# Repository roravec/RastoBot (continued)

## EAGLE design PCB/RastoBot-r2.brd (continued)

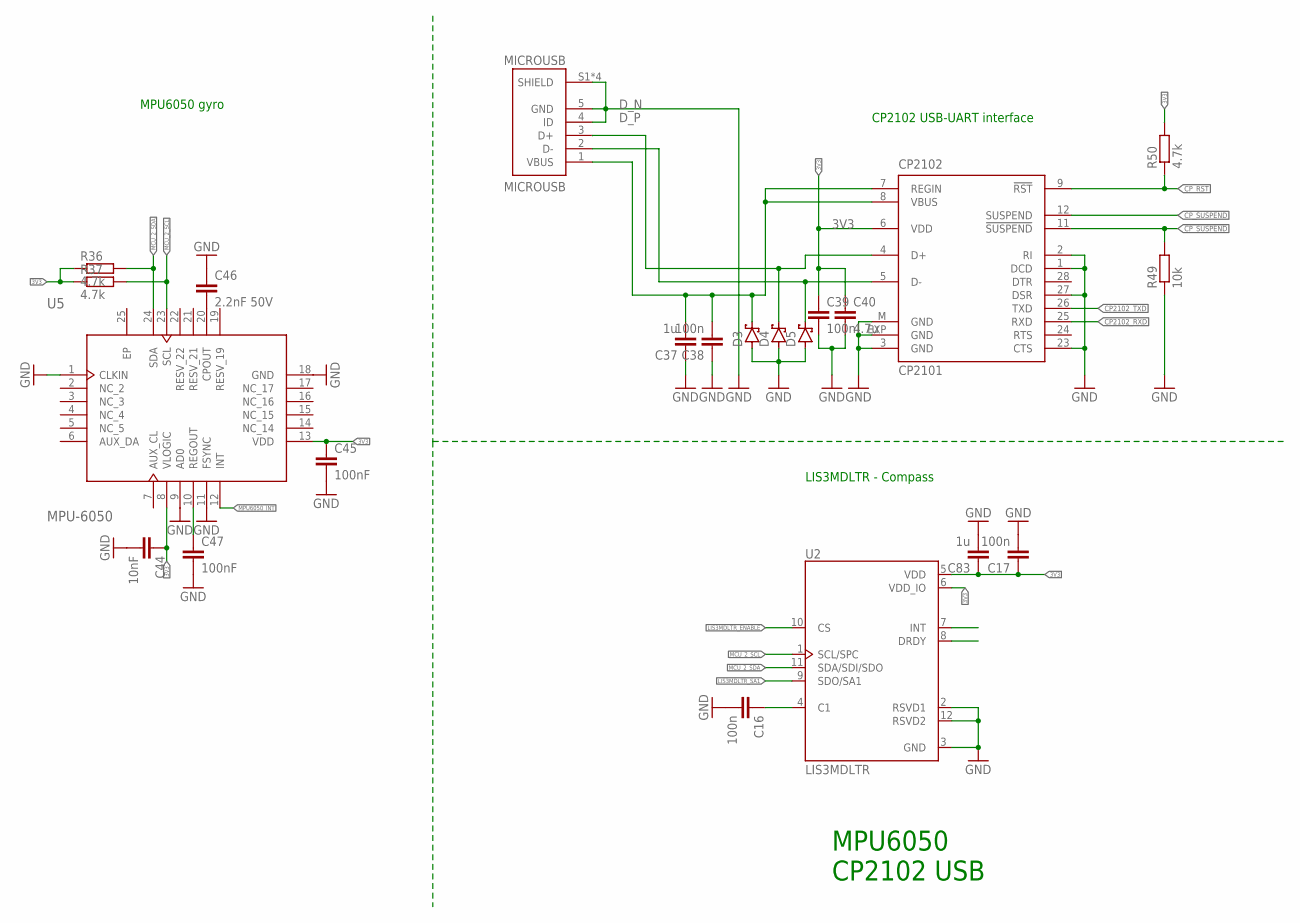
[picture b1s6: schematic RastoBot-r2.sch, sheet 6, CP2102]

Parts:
C16, C17, C38, C39: 100n; C0603
C37, C83: 1u; C0603
C40: 4.7u; C0603
C44: 10nF; C0603
C45, C47: 100nF; C0603
C46: 2.2nF 50V; C0603
CP2102: CP2101; MLP28
D3, D4, D5: BAT60J; SOD323_ST
MICROUSB: MICROUSB; MOLEX_47642-0001
R36, R37, R50: 4.7k; R0603
R49: 10k; R0603
U2: LIS3MDLTR; XDCR_LIS3MDLTR
U5: MPU-6050; 24-VFQFN

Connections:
3V3: C17.1, C39.1, C40.1, C44.1, C45.1, C83.1, CP2102.6 (VDD), R36.1, R37.1, R50.2, U2.5 (VDD), U2.6 (VDD_IO), U5.8 (VLOGIC), U5.13 (VDD); also elsewhere on the board
!CP_SUSPEND: CP2102.11 (!SUSPEND), R49.2
CP2102_RXD: CP2102.25 (RXD); also elsewhere on the board
CP2102_TXD: CP2102.26 (TXD); also elsewhere on the board
CP_RST: CP2102.9 (!RST), R50.1
CP_SUSPEND: CP2102.12 (SUSPEND)
D_N: CP2102.5 (D-), D5.C, MICROUSB.2 (D-)
D_P: CP2102.4 (D+), D4.C, MICROUSB.3 (D+)
EP: U5.25 (EP)
GND: C16.2, C17.2, C37.1, C38.1, C39.2, C40.2, C44.2, C45.2, C46.1, C47.2, C83.2, CP2102.1 (DCD), CP2102.2 (RI), CP2102.3 (GND), CP2102.23 (CTS), CP2102.27 (DSR), CP2102.EXP (GND), CP2102.M (GND), D3.A, D4.A, D5.A, MICROUSB.4 (ID), MICROUSB.5 (GND), MICROUSB.S1 (SHIELD), MICROUSB.S2 (SHIELD), MICROUSB.S3 (SHIELD), MICROUSB.S4 (SHIELD), R49.1, U2.2 (RSVD1), U2.3 (GND), U2.12 (RSVD2), U5.1 (CLKIN), U5.9 (AD0), U5.11 (FSYNC), U5.18 (GND); also elsewhere on the board
LIS3MDLTR_ENABLE: U2.10 (CS)
LIS3MDLTR_SA1: U2.9 (SDO/SA1)
MCU_2_SCL: R37.2, U2.1 (SCL/SPC), U5.23 (SCL); also elsewhere on the board
MCU_2_SDA: R36.2, U2.11 (SDA/SDI/SDO), U5.24 (SDA); also elsewhere on the board
MPU6050_INT: U5.12 (INT)
unnamed: C37.2, C38.2, CP2102.7 (REGIN), CP2102.8 (VBUS), D3.C, MICROUSB.1 (VBUS)
unnamed: C46.2, U5.20 (CPOUT)
unnamed: C47.1, U5.10 (REGOUT)
unnamed: C16.1, U2.4 (C1)

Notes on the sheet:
MPU6050 CP2102 USB
MPU6050 gyro
CP2102 USB-UART interface
LIS3MDLTR - Compass

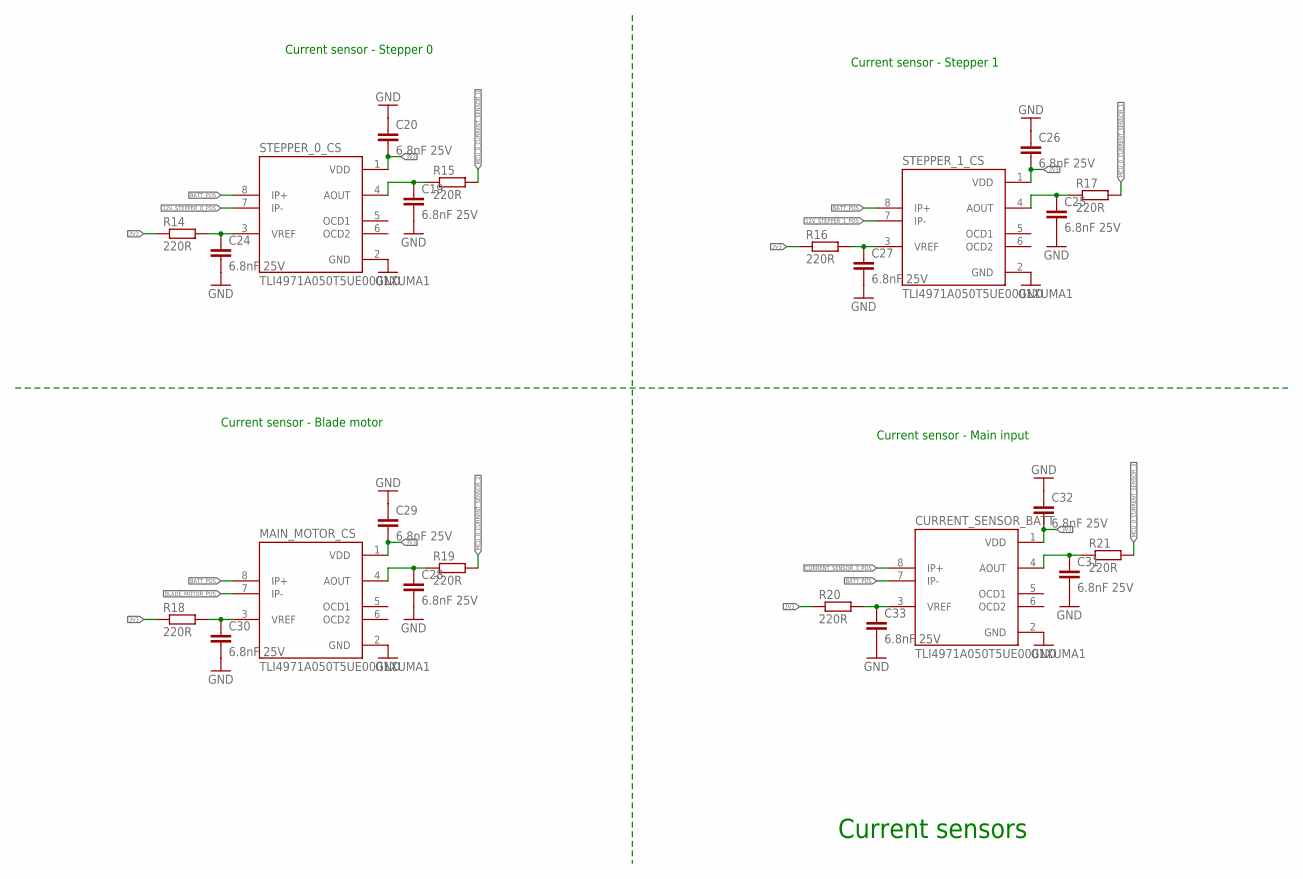
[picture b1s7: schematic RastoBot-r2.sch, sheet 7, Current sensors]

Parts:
C19, C20, C24, C25, C26, C27, C28, C29, C30, C31, C32, C33: 6.8nF 25V; C0603
CURRENT_SENSOR_BATT: TLI4971A050T5UE0001XUMA1; IC_TLI4971A050T5UE0001XUMA1
MAIN_MOTOR_CS: TLI4971A050T5UE0001XUMA1; IC_TLI4971A050T5UE0001XUMA1
R14, R15, R16, R17, R18, R19, R20, R21: 220R; R0805
STEPPER_0_CS, STEPPER_1_CS: TLI4971A050T5UE0001XUMA1; IC_TLI4971A050T5UE0001XUMA1

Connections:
3V3: C20.2, C26.2, C29.2, C32.2, CURRENT_SENSOR_BATT.1 (VDD), MAIN_MOTOR_CS.1 (VDD), R14.1, R16.1, R18.1, R20.1, STEPPER_0_CS.1 (VDD), STEPPER_1_CS.1 (VDD); also elsewhere on the board
12V_STEPPER_0_POS: STEPPER_0_CS.7 (IP-); also elsewhere on the board
12V_STEPPER_1_POS: STEPPER_1_CS.7 (IP-); also elsewhere on the board
BATT_POS: CURRENT_SENSOR_BATT.7 (IP-), MAIN_MOTOR_CS.8 (IP+), STEPPER_0_CS.8 (IP+), STEPPER_1_CS.8 (IP+); also elsewhere on the board
BLADE_MOTOR_POS: MAIN_MOTOR_CS.7 (IP-); also elsewhere on the board
CURRENT_SENSOR_3_POS: CURRENT_SENSOR_BATT.8 (IP+); also elsewhere on the board
GND: C19.2, C20.1, C24.2, C25.2, C26.1, C27.2, C28.2, C29.1, C30.2, C31.2, C32.1, C33.2, CURRENT_SENSOR_BATT.2 (GND), MAIN_MOTOR_CS.2 (GND), STEPPER_0_CS.2 (GND), STEPPER_1_CS.2 (GND); also elsewhere on the board
MCU_0_CURRENT_SENSOR_0: R15.2; also elsewhere on the board
MCU_0_CURRENT_SENSOR_1: R17.2; also elsewhere on the board
MCU_0_CURRENT_SENSOR_2: R19.2; also elsewhere on the board
MCU_0_CURRENT_SENSOR_3: R21.2; also elsewhere on the board
unnamed: C19.1, R15.1, STEPPER_0_CS.4 (AOUT)
unnamed: C27.1, R16.2, STEPPER_1_CS.3 (VREF)
unnamed: C25.1, R17.1, STEPPER_1_CS.4 (AOUT)
unnamed: C24.1, R14.2, STEPPER_0_CS.3 (VREF)
unnamed: C30.1, MAIN_MOTOR_CS.3 (VREF), R18.2
unnamed: C28.1, MAIN_MOTOR_CS.4 (AOUT), R19.1
unnamed: C33.1, CURRENT_SENSOR_BATT.3 (VREF), R20.2
unnamed: C31.1, CURRENT_SENSOR_BATT.4 (AOUT), R21.1

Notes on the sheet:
Current sensors
Current sensor - Stepper 0
Current sensor - Stepper 1
Current sensor - Blade motor
Current sensor - Main input

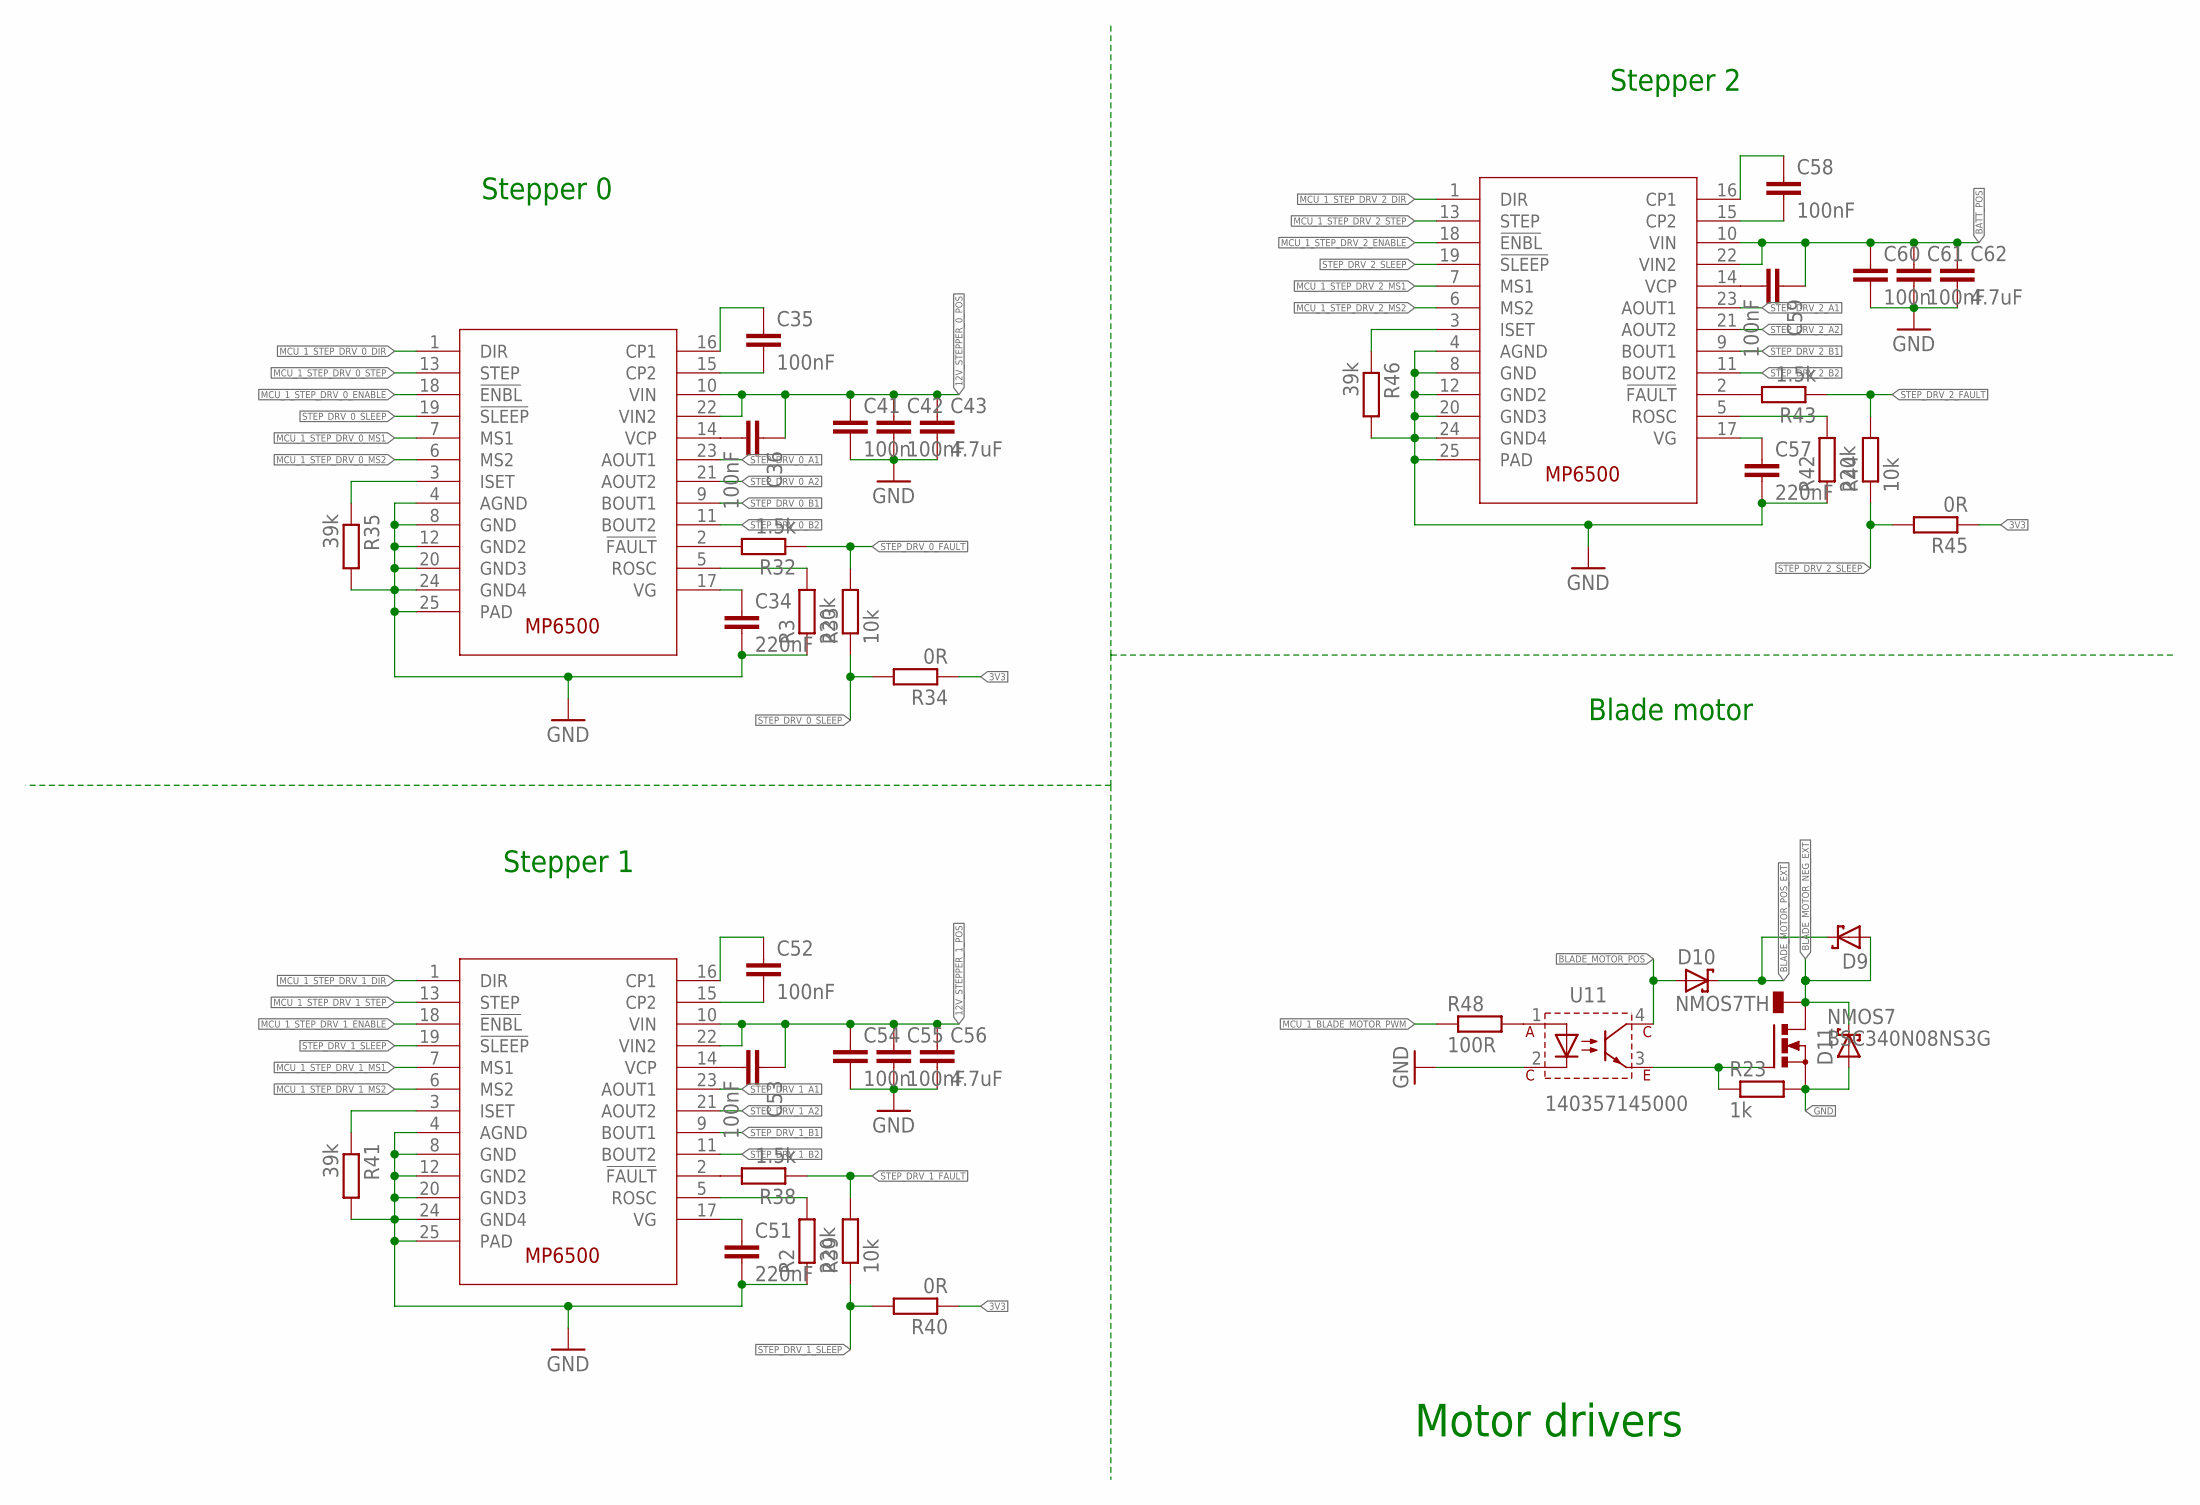
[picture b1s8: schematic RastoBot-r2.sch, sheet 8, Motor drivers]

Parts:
C34, C51, C57: 220nF; C0603
C35, C36, C42, C52, C53, C55, C58, C59, C61: 100nF; C0603
C41, C54, C60: 100n; C0603
C43, C56, C62: 4.7uF; C0603
D9, D10, D11: SCHOTTKY-DIODEAG; AG
NMOS7: BSC340N08NS3G; PG-TDSON-8
R2, R3, R42: 220k; R0603
R23: 1k; R0805
R32, R38, R43: 1.5k; R0603
R33, R39, R44: 10k; R0603
R34, R40, R45: 0R; R0603
R35, R41, R46: 39k; R0603
R48: 100R; R0805
SD1, SD2, SD3: MP6500; QFN65P500X500X100-25N
U11: 140357145000; WL-OCPT_SOP4

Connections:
3V3: R34.1, R40.1, R45.1; also elsewhere on the board
12V_STEPPER_0_POS: C36.1, C41.1, C42.1, C43.1, SD1.10 (VIN), SD1.22 (VIN2); also elsewhere on the board
12V_STEPPER_1_POS: C53.1, C54.1, C55.1, C56.1, SD2.10 (VIN), SD2.22 (VIN2); also elsewhere on the board
BATT_POS: C59.1, C60.1, C61.1, C62.1, SD3.10 (VIN), SD3.22 (VIN2); also elsewhere on the board
BLADE_MOTOR_NEG_EXT: D9.A, D11.C, NMOS7.5 (D), NMOS7.6 (D), NMOS7.7 (D), NMOS7.8 (D), NMOS7.TH; also elsewhere on the board
BLADE_MOTOR_POS: D10.A, U11.4; also elsewhere on the board
BLADE_MOTOR_POS_EXT: D9.C, D10.C; also elsewhere on the board
GND: C34.2, C41.2, C42.2, C43.2, C51.2, C54.2, C55.2, C56.2, C57.2, C60.2, C61.2, C62.2, D11.A, NMOS7.1 (S), NMOS7.2 (S), NMOS7.3 (S), R2.1, R3.1, R23.2, R35.2, R41.2, R42.1, R46.2, SD1.4 (AGND), SD1.8 (GND), SD1.12 (GND2), SD1.20 (GND3), SD1.24 (GND4), SD1.25 (PAD), SD2.4 (AGND), SD2.8 (GND), SD2.12 (GND2), SD2.20 (GND3), SD2.24 (GND4), SD2.25 (PAD), SD3.4 (AGND), SD3.8 (GND), SD3.12 (GND2), SD3.20 (GND3), SD3.24 (GND4), SD3.25 (PAD), U11.2; also elsewhere on the board
MCU_1_BLADE_MOTOR_PWM: R48.1; also elsewhere on the board
MCU_1_STEP_DRV_0_DIR: SD1.1 (DIR); also elsewhere on the board
MCU_1_STEP_DRV_0_ENABLE: SD1.18 (!ENBL); also elsewhere on the board
MCU_1_STEP_DRV_0_MS1: SD1.7 (MS1); also elsewhere on the board
MCU_1_STEP_DRV_0_MS2: SD1.6 (MS2); also elsewhere on the board
MCU_1_STEP_DRV_0_STEP: SD1.13 (STEP); also elsewhere on the board
MCU_1_STEP_DRV_1_DIR: SD2.1 (DIR); also elsewhere on the board
MCU_1_STEP_DRV_1_ENABLE: SD2.18 (!ENBL); also elsewhere on the board
MCU_1_STEP_DRV_1_MS1: SD2.7 (MS1); also elsewhere on the board
MCU_1_STEP_DRV_1_MS2: SD2.6 (MS2); also elsewhere on the board
MCU_1_STEP_DRV_1_STEP: SD2.13 (STEP); also elsewhere on the board
MCU_1_STEP_DRV_2_DIR: SD3.1 (DIR); also elsewhere on the board
MCU_1_STEP_DRV_2_ENABLE: SD3.18 (!ENBL); also elsewhere on the board
MCU_1_STEP_DRV_2_MS1: SD3.7 (MS1); also elsewhere on the board
MCU_1_STEP_DRV_2_MS2: SD3.6 (MS2); also elsewhere on the board
MCU_1_STEP_DRV_2_STEP: SD3.13 (STEP); also elsewhere on the board
unnamed: C34.1, SD1.17 (VG)
unnamed: R3.2, SD1.5 (ROSC)
unnamed: R48.2, U11.1
unnamed: NMOS7.4 (G), R23.1, U11.3
unnamed: C35.2, SD1.15 (CP2)
unnamed: C35.1, SD1.16 (CP1)
unnamed: R32.2, SD1.2 (!FAULT)
unnamed: C36.2, SD1.14 (VCP)
unnamed: C51.1, SD2.17 (VG)
unnamed: R35.1, SD1.3 (ISET)
unnamed: R2.2, SD2.5 (ROSC)
unnamed: C52.2, SD2.15 (CP2)
unnamed: C52.1, SD2.16 (CP1)
unnamed: C53.2, SD2.14 (VCP)
unnamed: R41.1, SD2.3 (ISET)
unnamed: R38.2, SD2.2 (!FAULT)
unnamed: C57.1, SD3.17 (VG)
unnamed: R42.2, SD3.5 (ROSC)
unnamed: C58.2, SD3.15 (CP2)
unnamed: C58.1, SD3.16 (CP1)
unnamed: C59.2, SD3.14 (VCP)
unnamed: R46.1, SD3.3 (ISET)
unnamed: R43.2, SD3.2 (!FAULT)
STEP_DRV_0_A1: SD1.23 (AOUT1); also elsewhere on the board
STEP_DRV_0_A2: SD1.21 (AOUT2); also elsewhere on the board
STEP_DRV_0_B1: SD1.9 (BOUT1); also elsewhere on the board
STEP_DRV_0_B2: SD1.11 (BOUT2); also elsewhere on the board
STEP_DRV_0_FAULT: R32.1, R33.2
STEP_DRV_0_SLEEP: R33.1, R34.2, SD1.19 (!SLEEP)
STEP_DRV_1_A1: SD2.23 (AOUT1); also elsewhere on the board
STEP_DRV_1_A2: SD2.21 (AOUT2); also elsewhere on the board
STEP_DRV_1_B1: SD2.9 (BOUT1); also elsewhere on the board
STEP_DRV_1_B2: SD2.11 (BOUT2); also elsewhere on the board
STEP_DRV_1_FAULT: R38.1, R39.2
STEP_DRV_1_SLEEP: R39.1, R40.2, SD2.19 (!SLEEP)
STEP_DRV_2_A1: SD3.23 (AOUT1); also elsewhere on the board
STEP_DRV_2_A2: SD3.21 (AOUT2); also elsewhere on the board
STEP_DRV_2_B1: SD3.9 (BOUT1); also elsewhere on the board
STEP_DRV_2_B2: SD3.11 (BOUT2); also elsewhere on the board
STEP_DRV_2_FAULT: R43.1, R44.2
STEP_DRV_2_SLEEP: R44.1, R45.2, SD3.19 (!SLEEP)

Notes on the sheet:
Stepper 0
Stepper 1
Stepper 2
Blade motor
Motor drivers

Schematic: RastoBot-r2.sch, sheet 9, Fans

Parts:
EM_LIGHT: EMERGENCY LIGHT; 1X02
FAN_0: FAN_0; 1X02
FAN_1: FAN_1; 1X02
FAN_2: FAN_2; 1X02
FAN_3: FAN_3; 1X02
NMOS2, NMOS3, NMOS4, NMOS5, NMOS6: BSC340N08NS3G; PG-TDSON-8
R22, R51, R52, R53, R119: 200R; R0805
R63, R65, R67, R68, R76: 1k; R0805
U4, U6, U7, U8, U12: 140357145000; WL-OCPT_SOP4

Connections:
BATT_POS: EM_LIGHT.1, FAN_0.1, FAN_1.1, FAN_2.1, FAN_3.1, U4.4, U6.4, U7.4, U8.4, U12.4; also elsewhere on the board
GND: NMOS2.1 (S), NMOS2.2 (S), NMOS2.3 (S), NMOS3.1 (S), NMOS3.2 (S), NMOS3.3 (S), NMOS4.1 (S), NMOS4.2 (S), NMOS4.3 (S), NMOS5.1 (S), NMOS5.2 (S), NMOS5.3 (S), NMOS6.1 (S), NMOS6.2 (S), NMOS6.3 (S), R63.2, R65.2, R67.2, R68.2, R76.2, U4.2, U6.2, U7.2, U8.2, U12.2; also elsewhere on the board
MCU_0_EMERGENCY_LIGHT: R119.1; also elsewhere on the board
MCU_0_FAN_0: R22.1; also elsewhere on the board
MCU_0_FAN_1: R51.1; also elsewhere on the board
MCU_0_FAN_2: R53.1; also elsewhere on the board
MCU_0_FAN_3: R52.1; also elsewhere on the board
unnamed: NMOS6.4 (G), R68.1, U12.3
unnamed: EM_LIGHT.2, NMOS6.5 (D), NMOS6.6 (D), NMOS6.7 (D), NMOS6.8 (D), NMOS6.TH
unnamed: R119.2, U12.1
unnamed: R22.2, U4.1
unnamed: FAN_0.2, NMOS2.5 (D), NMOS2.6 (D), NMOS2.7 (D), NMOS2.8 (D), NMOS2.TH
unnamed: R51.2, U6.1
unnamed: R52.2, U8.1
unnamed: NMOS2.4 (G), R76.1, U4.3
unnamed: NMOS3.4 (G), R63.1, U6.3
unnamed: FAN_1.2, NMOS3.5 (D), NMOS3.6 (D), NMOS3.7 (D), NMOS3.8 (D), NMOS3.TH
unnamed: R53.2, U7.1
unnamed: NMOS4.4 (G), R65.1, U7.3
unnamed: FAN_2.2, NMOS4.5 (D), NMOS4.6 (D), NMOS4.7 (D), NMOS4.8 (D), NMOS4.TH
unnamed: NMOS5.4 (G), R67.1, U8.3
unnamed: FAN_3.2, NMOS5.5 (D), NMOS5.6 (D), NMOS5.7 (D), NMOS5.8 (D), NMOS5.TH

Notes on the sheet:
Fan_0
Fan_1
Fan_2
Fan_3
Fan drivers Emergency light switch
Emergency light

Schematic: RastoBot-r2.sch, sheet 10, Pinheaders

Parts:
C63, C64, C65, C66: 1u; C0603
D2: 3V3; SOD80C
GPS: GPS MODULE; 1X05
LIDAR: LIDAR; 1X08
LIGHT_SENSOR: PHOTORESISTOR LDR5549; 1X02
LIMIT_SWITCH_DOWN: LIMIT_SWITCH_BOTTOM_MAGNETIC; 1X03
LIMIT_SWITCH_UP: LIMIT_SWITCH_UPPER_MAGNETIC; 1X03
MAIN_MOTOR: MAIN MOTOR; 1X04
MCU_2_I2C_EXTENDER: MCU_2_I2C_EXTENDER; 1X04
NAVIGATION_UART: TELEMETRY_UART; 1X02
NMOS1: BSC340N08NS3G; PG-TDSON-8
PERIMETER_WIRE: PER.WIRE SENSE; 1X04
R4, R54: 1k; R0805
R55, R64: 500k; R0805
R57, R66: 10R; R0805
R62: 200R; R0805
R69, R71, R72: 5k; R0805
R70: 5k; R0603
R107, R108, R109, R110: 10k; R0805
RAIN_SENSOR: RAIN SENSOR; 1X02
STEPPER_0: STEPPER_0; 1X04
STEPPER_1: STEPPER_1; 1X04
STEPPER_2: STEPPER_2; 1X04
TEMP_SENSOR_0: TEMP SENSOR 0; 1X03
TEMP_SENSOR_1: TEMP SENSOR 1; 1X03
TEMP_SENSOR_2: TEMP SENSOR 2; 1X03
TEMP_SENSOR_3: TEMP SENSOR 3; 1X03
U10: 140357145000; WL-OCPT_SOP4
UNLIMITED_POWER: V_OUTPUT; 1X05

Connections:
3V3: C63.2, C64.2, C65.2, C66.2, GPS.1, LIMIT_SWITCH_DOWN.1, LIMIT_SWITCH_UP.1, MCU_2_I2C_EXTENDER.3, R55.1, R64.1, R69.2, R70.2, R71.2, R72.2, TEMP_SENSOR_0.1, TEMP_SENSOR_1.1, TEMP_SENSOR_2.1, TEMP_SENSOR_3.1, UNLIMITED_POWER.1; also elsewhere on the board
5V: LIDAR.2, PERIMETER_WIRE.1, U10.4, UNLIMITED_POWER.2; also elsewhere on the board
BATT_POS: UNLIMITED_POWER.3; also elsewhere on the board
BLADE_MOTOR_NEG_EXT: MAIN_MOTOR.3, MAIN_MOTOR.4; also elsewhere on the board
BLADE_MOTOR_POS_EXT: MAIN_MOTOR.1, MAIN_MOTOR.2; also elsewhere on the board
GND: C63.1, C64.1, C65.1, C66.1, D2.A, GPS.2, LIDAR.1, LIGHT_SENSOR.2, LIMIT_SWITCH_DOWN.3, LIMIT_SWITCH_UP.3, MCU_2_I2C_EXTENDER.4, NMOS1.1 (S), NMOS1.2 (S), NMOS1.3 (S), PERIMETER_WIRE.3, PERIMETER_WIRE.4, R54.2, R109.1, R110.1, RAIN_SENSOR.2, TEMP_SENSOR_0.3, TEMP_SENSOR_1.3, TEMP_SENSOR_2.3, TEMP_SENSOR_3.3, U10.2, UNLIMITED_POWER.4, UNLIMITED_POWER.5; also elsewhere on the board
GPS_PPS: GPS.5
GPS_RXD: GPS.4; also elsewhere on the board
GPS_TXD: GPS.3; also elsewhere on the board
LIDAR_RX: LIDAR.4; also elsewhere on the board
LIDAR_TX: LIDAR.7; also elsewhere on the board
LIMIT_SWITCH_BOTTOM: R108.1; also elsewhere on the board
LIMIT_SWITCH_UPPER: R107.1; also elsewhere on the board
MCU_0_LIGHT_SENSOR: R66.1; also elsewhere on the board
MCU_0_RAIN_SENSOR: R57.1; also elsewhere on the board
MCU_0_TEMP_SENSOR_0: R69.1, TEMP_SENSOR_0.2; also elsewhere on the board
MCU_0_TEMP_SENSOR_1: R70.1, TEMP_SENSOR_1.2; also elsewhere on the board
MCU_0_TEMP_SENSOR_2: R71.1, TEMP_SENSOR_2.2; also elsewhere on the board
MCU_0_TEMP_SENSOR_3: R72.1, TEMP_SENSOR_3.2; also elsewhere on the board
MCU_2_LIDAR_ENABLE: R62.1; also elsewhere on the board
MCU_2_SCL: MCU_2_I2C_EXTENDER.2; also elsewhere on the board
MCU_2_SDA: MCU_2_I2C_EXTENDER.1; also elsewhere on the board
MCU_3_UART2_RX: NAVIGATION_UART.1; also elsewhere on the board
MCU_3_UART2_TX: NAVIGATION_UART.2; also elsewhere on the board
unnamed: PERIMETER_WIRE.2, R4.2
unnamed: LIDAR.5, NMOS1.5 (D), NMOS1.6 (D), NMOS1.7 (D), NMOS1.8 (D), NMOS1.TH
unnamed: LIGHT_SENSOR.1, R64.2, R66.2
unnamed: NMOS1.4 (G), R54.1, U10.3
unnamed: R55.2, R57.2, RAIN_SENSOR.1
unnamed: R62.2, U10.1
unnamed: LIMIT_SWITCH_DOWN.2, R108.2, R109.2
unnamed: LIMIT_SWITCH_UP.2, R107.2, R110.2
PERIMETER_WIRE_SENSE: D2.C, R4.1; also elsewhere on the board
STEP_DRV_0_A1: STEPPER_0.1; also elsewhere on the board
STEP_DRV_0_A2: STEPPER_0.2; also elsewhere on the board
STEP_DRV_0_B1: STEPPER_0.3; also elsewhere on the board
STEP_DRV_0_B2: STEPPER_0.4; also elsewhere on the board
STEP_DRV_1_A1: STEPPER_1.1; also elsewhere on the board
STEP_DRV_1_A2: STEPPER_1.2; also elsewhere on the board
STEP_DRV_1_B1: STEPPER_1.3; also elsewhere on the board
STEP_DRV_1_B2: STEPPER_1.4; also elsewhere on the board
STEP_DRV_2_A1: STEPPER_2.1; also elsewhere on the board
STEP_DRV_2_A2: STEPPER_2.2; also elsewhere on the board
STEP_DRV_2_B1: STEPPER_2.3; also elsewhere on the board
STEP_DRV_2_B2: STEPPER_2.4; also elsewhere on the board

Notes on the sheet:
GPS TXD to MCU RX!
Resistance is between 10M (dry) to less than 1M (fully wet)
Blade motor
Stepper_0
Stepper_1
Stepper_2
GPS
Rain sensor
Mechanical limit switches
Temperature sensor DHT11
Perimeter wire sense
Lidar
Magnetic limit switches
Pinheaders
Resistance is between 10M (dark) to less than 100k (daylight)
Light sensor
MCU_2_I2C Extender

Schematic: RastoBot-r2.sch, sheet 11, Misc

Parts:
BATT: TPB1,27; B1,27
BATT_POS: TPB1,27; B1,27
CP2102_RX, CP2102_TX: TPB1,27; B1,27
CS_BATT: TPB1,27; B1,27
CS_MAIN_MOT: TPB1,27; B1,27
CS_STEP0, CS_STEP1: TPB1,27; B1,27
GPS_RX: TPB1,27; B1,27
GPS_TX: TPB1,27; B1,27
H1, H2, H3, H4, H5, H6: MOUNT-PAD-ROUND3.0; 3,0-PAD
LIDAR_RX: TPB1,27; B1,27
LIDAR_TX: TPB1,27; B1,27
MCU0_RX, MCU0_TX, MCU1_RX, MCU1_TX, MCU3_RX, MCU3_SCL, MCU3_SDA, MCU3_TX: TPB1,27; B1,27
MPU6050_SCL, MPU6050_SDA: TPB1,27; B1,27
PERIM: TPB1,27; B1,27
TILT: TPB1,27; B1,27
TP2, TP3: TPB1,27; B1,27

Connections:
3V3: TP3.TP; also elsewhere on the board
5V: TP2.TP; also elsewhere on the board
BATT_DIRECT_POS_POLE: BATT.TP; also elsewhere on the board
BATT_POS: BATT_POS.TP; also elsewhere on the board
CP2102_RXD: CP2102_RX.TP; also elsewhere on the board
CP2102_TXD: CP2102_TX.TP; also elsewhere on the board
GPS_RXD: GPS_RX.TP; also elsewhere on the board
GPS_TXD: GPS_TX.TP; also elsewhere on the board
LIDAR_RX: LIDAR_RX.TP; also elsewhere on the board
LIDAR_TX: LIDAR_TX.TP; also elsewhere on the board
MCU_0_CURRENT_SENSOR_0: CS_STEP0.TP; also elsewhere on the board
MCU_0_CURRENT_SENSOR_1: CS_STEP1.TP; also elsewhere on the board
MCU_0_CURRENT_SENSOR_2: CS_MAIN_MOT.TP; also elsewhere on the board
MCU_0_CURRENT_SENSOR_3: CS_BATT.TP; also elsewhere on the board
MCU_0_TILT_SENSOR: TILT.TP; also elsewhere on the board
MCU_0_UART_RX: MCU0_RX.TP; also elsewhere on the board
MCU_0_UART_TX: MCU0_TX.TP; also elsewhere on the board
MCU_1_UART1_RX: MCU1_RX.TP; also elsewhere on the board
MCU_1_UART1_TX: MCU1_TX.TP; also elsewhere on the board
MCU_2_SCL: MPU6050_SCL.TP; also elsewhere on the board
MCU_2_SDA: MPU6050_SDA.TP; also elsewhere on the board
MCU_3_I2C_SCL: MCU3_SCL.TP; also elsewhere on the board
MCU_3_I2C_SDA: MCU3_SDA.TP; also elsewhere on the board
MCU_3_UART1_RX: MCU3_RX.TP; also elsewhere on the board
MCU_3_UART1_TX: MCU3_TX.TP; also elsewhere on the board
PERIMETER_WIRE_SENSE: PERIM.TP; also elsewhere on the board

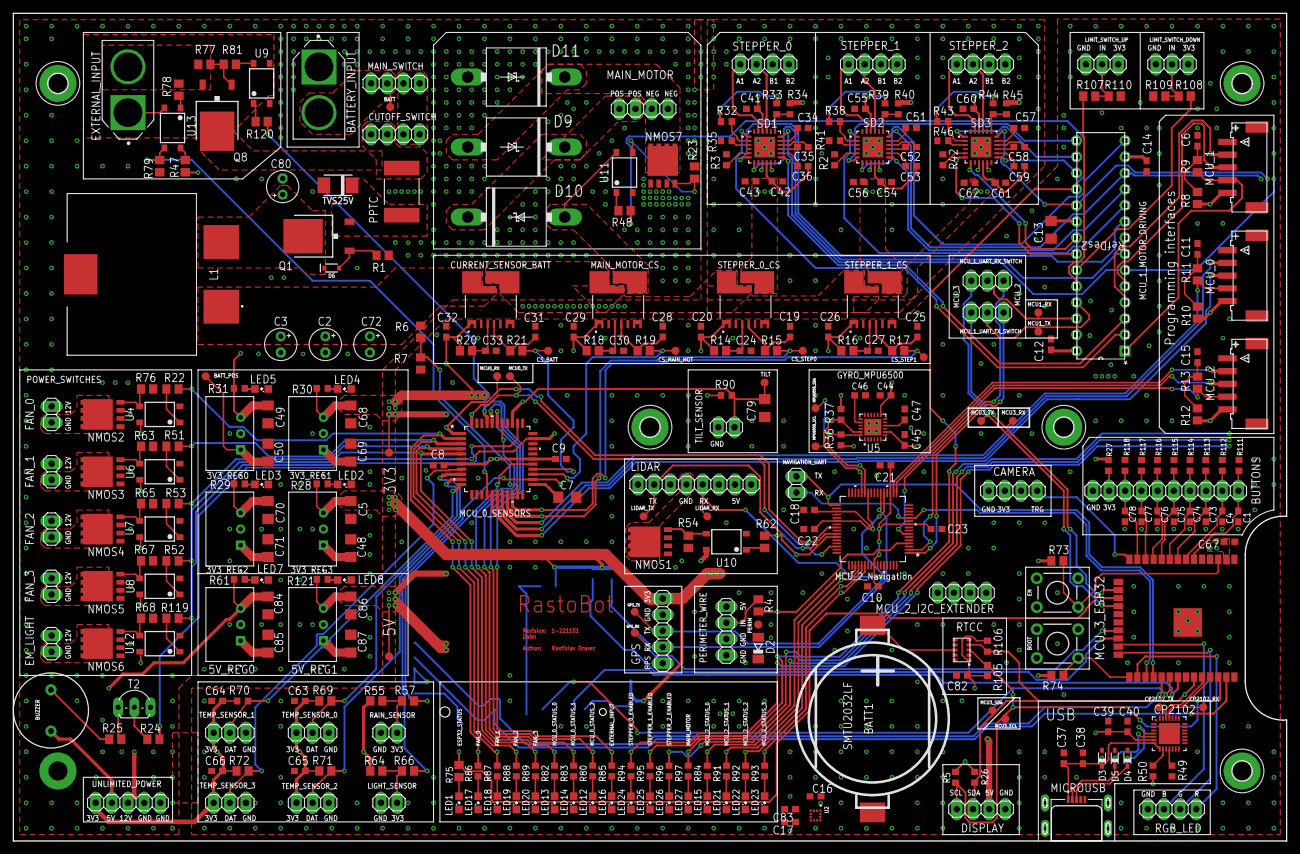
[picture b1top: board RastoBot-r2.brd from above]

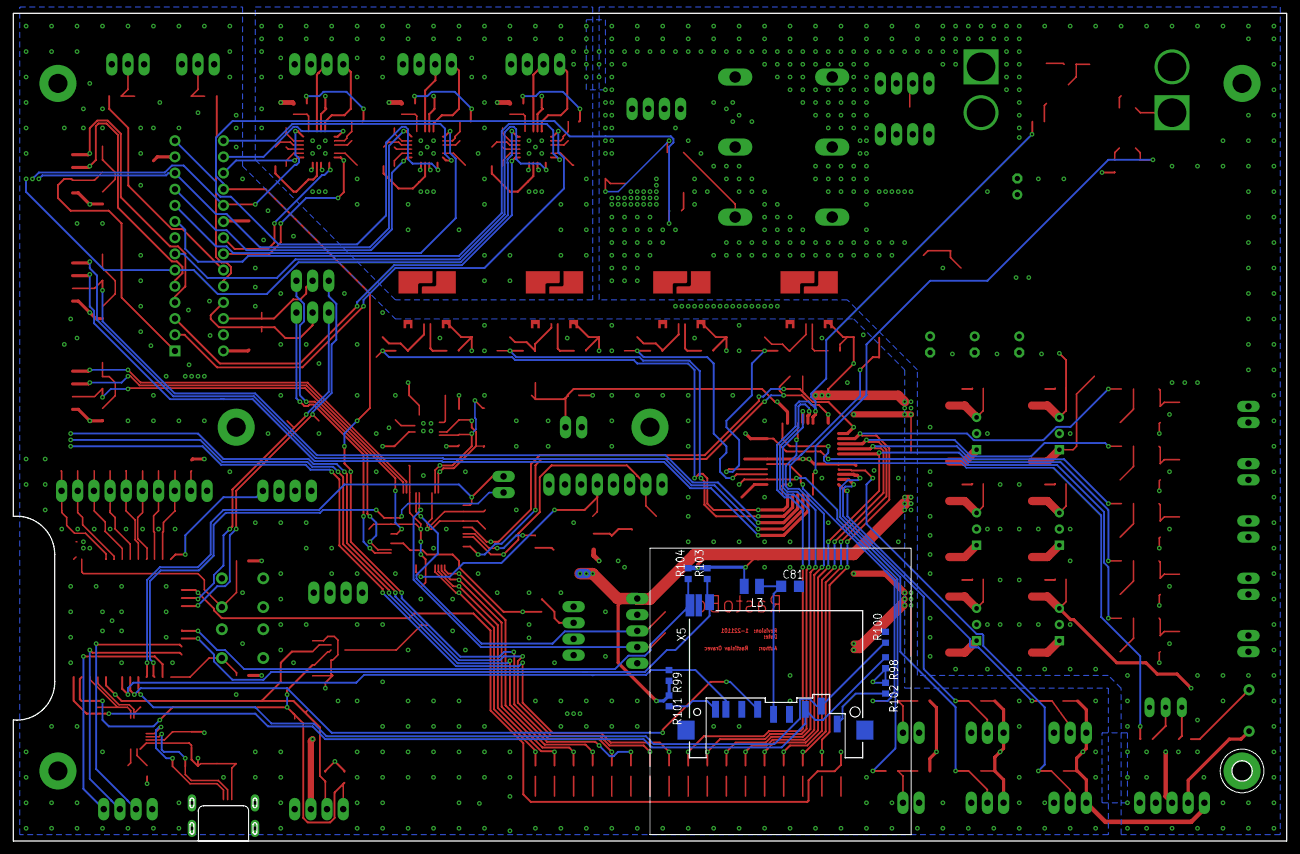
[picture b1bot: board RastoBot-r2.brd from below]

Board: 4 copper layers, 200.0 x 130.0 mm, 354 parts (11 on the bottom side), 236 nets.

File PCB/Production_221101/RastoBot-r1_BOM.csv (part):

"Qty";"Value";"Device";"Package";"Parts";"Description";"ARROW_PART_NUMBER";"ARROW_PRICE-STOCK";"AVAILABILITY";"COPYRIGHT";"CREATED_BY";"CTR-MAX";"CTR-MIN";"DATASHEET-URL";"DESCRIPTION";"DIGIKEY_PART_NUMBER";"HEIGHT";"IF";"MANUFACTURER";"MANUFACTURER_NAME";"MANUFACTURER_PART_NUMBER";"MF";"MFR_NAME";"MOUNT";"MOUSER_PART_NUMBER";"MOUSER_PRICE-STOCK";"MP";"MPN";"OC_FARNELL";"OC_NEWARK";"PACKAGE";"PART-NUMBER";"POPULARITY";"PRICE";"PROD_ID";"PURCHASE-URL";"SF_SKU";"SPICEPREFIX";"TC-CTR";"TP_SIGNAL_NAME";"VALUE";"VCE";"VISO";
"1";"";"AB-RTCMC-32.768KHZ-B5ZE-S3-T";"AB-RTCMC-32.768KHZ-B5ZE-S3-T";"RTCC";"";"";"";"";"";"";"";"";"";"";"";"";"";"";"";"";"";"";"";"";"";"";"";"";"";"";"";"";"";"";"";"";"";"";"";"";"";"";
"23";"";"LEDSML0805";"SML0805";"LED1, LED2, LED3, LED4, LED5, LED7, LED8, LED12, LED13, LED14, LED15, LED16, LED17, LED18, LED19, LED20, LED21, LED22, LED23, LED24, LED25, LED26, LED27";"LED";"";"";"";"";"";"";"";"";"";"";"";"";"";"";"";"";"";"";"";"";"";"";"";"";"";"";"17";"";"";"";"";"";"";"";"";"";"";
"3";"";"SCHOTTKY-DIODEAG";"AG";"D9, D10, D11";"Schottky Diode";"";"";"";"";"";"";"";"";"";"";"";"";"";"";"";"";"";"";"";"";"";"";"";"";"";"";"";"";"";"";"";"";"";"";"";"";"";
"3";"0R";"R-EU_R0603";"R0603";"R34, R40, R45";"RESISTOR, European symbol";"";"";"";"";"";"";"";"";"";"";"";"";"";"";"";"";"";"";"";"";"";"";"";"";"";"";"70";"";"";"";"";"R";"";"";"";"";"";
"3";"1.5k";"R-EU_R0603";"R0603";"R32, R38, R43";"RESISTOR, European symbol";"";"";"";"";"";"";"";"";"";"";"";"";"";"";"";"";"";"";"";"";"";"";"";"";"";"";"70";"";"";"";"";"R";"";"";"";"";"";
"6";"100R";"R-EU_R0603";"R0603";"R28, R29, R30, R31, R61, R121";"RESISTOR, European symbol";"";"";"";"";"";"";"";"";"";"";"";"";"";"";"";"";"";"";"";"";"";"";"";"";"";"";"70";"";"";"";"";"R";"";"";"";"";"";
"5";"100R";"R-EU_R0805";"R0805";"R1, R11, R24, R25, R48";"RESISTOR, European symbol";"";"";"";"";"";"";"";"";"";"";"";"";"";"";"";"";"";"";"";"";"";"";"";"";"";"";"86";"";"";"";"";"R";"";"";"";"";"";
"5";"100n";"C-EUC0603";"C0603";"C38, C39, C41, C54, C60";"CAPACITOR, European symbol";"";"";"";"";"";"";"";"";"";"";"";"";"";"";"";"";"";"";"";"";"";"";"";"";"";"";"73";"";"";"";"";"C";"";"";"";"";"";
"7";"100n";"C-EUC0603";"C0603";"C10, C18, C21, C22, C23, C67, C82";"CAPACITOR, European symbol";"";"";"";"";"";"";"";"";"";"";"";"";"";"";"";"";"";"";"";"";"";"";"";"";"";"";"";"";"";"";"";"";"";"";"";"";"";
"1";"100n";"C-EUC1206";"C1206";"C79";"CAPACITOR, European symbol";"";"";"";"";"";"";"";"";"";"";"";"";"";"";"";"";"";"";"";"";"";"";"";"";"";"";"54";"";"";"";"";"C";"";"";"";"";"";
"18";"100nF";"C-EUC0603";"C0603";"C6, C8, C9, C11, C12, C14, C15, C35, C36, C42, C45, C47, C52, C53, C55, C58, C59, C61";"CAPACITOR, European symbol";"";"";"";"";"";"";"";"";"";"";"";"";"";"";"";"";"";"";"";"";"";"";"";"";"";"";"73";"";"";"";"";"C";"";"";"";"";"";
"2";"10R";"R-EU_R0805";"R0805";"R57, R66";"RESISTOR, European symbol";"";"";"";"";"";"";"";"";"";"";"";"";"";"";"";"";"";"";"";"";"";"";"";"";"";"";"86";"";"";"";"";"R";"";"";"";"";"";
"13";"10k";"R-EU_R0603";"R0603";"R33, R39, R44, R49, R90, R111, R112, R113, R114, R115, R116, R117, R118";"RESISTOR, European symbol";"";"";"";"";"";"";"";"";"";"";"";"";"";"";"";"";"";"";"";"";"";"";"";"";"";"";"70";"";"";"";"";"R";"";"";"";"";"";
"4";"10k";"R-EU_R0603";"R0603";"R98, R99, R103, R104";"RESISTOR, European symbol";"";"";"";"";"";"";"";"";"";"";"";"";"";"";"";"";"";"";"";"";"";"";"";"";"";"";"";"";"";"";"";"";"";"";"";"";"";
"9";"10k";"R-EU_R0805";"R0805";"R8, R10, R12, R47, R79, R107, R108, R109, R110";"RESISTOR, European symbol";"";"";"";"";"";"";"";"";"";"";"";"";"";"";"";"";"";"";"";"";"";"";"";"";"";"";"86";"";"";"";"";"R";"";"";"";"";"";
"8";"10n";"C-EUC0603";"C0603";"C1, C4, C73, C74, C75, C76, C77, C78";"CAPACITOR, European symbol";"";"";"";"";"";"";"";"";"";"";"";"";"";"";"";"";"";"";"";"";"";"";"";"";"";"";"73";"";"";"";"";"C";"";"";"";"";"";
"1";"10nF";"C-EUC0603";"C0603";"C44";"CAPACITOR, European symbol";"";"";"";"";"";"";"";"";"";"";"";"";"";"";"";"";"";"";"";"";"";"";"";"";"";"";"73";"";"";"";"";"C";"";"";"";"";"";
"2";"10u 6.3V";"C-EUC1206";"C1206";"C7, C13";"CAPACITOR, European symbol";"";"";"";"";"";"";"";"";"";"";"";"";"";"";"";"";"";"";"";"";"";"";"";"";"";"";"54";"";"";"";"";"C";"";"";"";"";"";
"1";"110k";"R-EU_R0805";"R0805";"R7";"RESISTOR, European symbol";"";"";"";"";"";"";"";"";"";"";"";"";"";"";"";"";"";"";"";"";"";"";"";"";"";"";"86";"";"";"";"";"R";"";"";"";"";"";
"2";"12k";"R-EU_R0805";"R0805";"R73, R74";"RESISTOR, European symbol";"";"";"";"";"";"";"";"";"";"";"";"";"";"";"";"";"";"";"";"";"";"";"";"";"";"";"86";"";"";"";"";"R";"";"";"";"";"";
"16";"130R";"R-EU_R0603";"R0603";"R80, R82, R83, R84, R85, R86, R87, R88, R89, R91, R92, R93, R94, R95, R96, R97";"RESISTOR, European symbol";"";"";"";"";"";"";"";"";"";"";"";"";"";"";"";"";"";"";"";"";"";"";"";"";"";"";"70";"";"";"";"";"R";"";"";"";"";"";
"9";"140357145000";"WL-OCPT_SERIES_357_140357145000";"WL-OCPT_SOP4";"U4, U6, U7, U8, U9, U10, U11, U12, U13";"WL-OCPT SOP-4";"";"";"";"";"";"600%";"50%";"https://www.we-online.com/redexpert/spec/140357145000?ae";"";"";"";"60mA";"";"";"";"";"";"SMT";"";"";"";"";"";"";"";"140357145000";"";"";"";"";"";"";"IF = 5mA,VCE = 5 V";"";"140357145000";"35V";"3750(V(RMS))";
"1";"1M";"R-EU_R0603";"R0603";"R100";"RESISTOR, European symbol";"";"";"";"";"";"";"";"";"";"";"";"";"";"";"";"";"";"";"";"";"";"";"";"";"";"";"";"";"";"";"";"";"";"";"";"";"";
"1";"1M";"R-EU_R0805";"R0805";"R6";"RESISTOR, European symbol";"";"";"";"";"";"";"";"";"";"";"";"";"";"";"";"";"";"";"";"";"";"";"";"";"";"";"86";"";"";"";"";"R";"";"";"";"";"";
"1";"1k";"R-EU_R0603";"R0603";"R27";"RESISTOR, European symbol";"";"";"";"";"";"";"";"";"";"";"";"";"";"";"";"";"";"";"";"";"";"";"";"";"";"";"70";"";"";"";"";"R";"";"";"";"";"";
"10";"1k";"R-EU_R0805";"R0805";"R4, R9, R13, R23, R54, R63, R65, R67, R68, R76";"RESISTOR, European symbol";"";"";"";"";"";"";"";"";"";"";"";"";"";"";"";"";"";"";"";"";"";"";"";"";"";"";"86";"";"";"";"";"R";"";"";"";"";"";
"5";"1u";"C-EUC0603";"C0603";"C37, C63, C64, C65, C66";"CAPACITOR, European symbol";"";"";"";"";"";"";"";"";"";"";"";"";"";"";"";"";"";"";"";"";"";"";"";"";"";"";"73";"";"";"";"";"C";"";"";"";"";"";
"1";"2.2nF 50V";"C-EUC0603";"C0603";"C46";"CAPACITOR, European symbol";"";"";"";"";"";"";"";"";"";"";"";"";"";"";"";"";"";"";"";"";"";"";"";"";"";"";"73";"";"";"";"";"C";"";"";"";"";"";
"8";"200R";"R-EU_R0805";"R0805";"R22, R51, R52, R53, R62, R78, R119, R120";"RESISTOR, European symbol";"";"";"";"";"";"";"";"";"";"";"";"";"";"";"";"";"";"";"";"";"";"";"";"";"";"";"86";"";"";"";"";"R";"";"";"";"";"";
"1";"2112805";"L-EUL2825P";"L2825P";"L3";"INDUCTOR, European symbol";"";"";"";"";"";"";"";"";"";"";"";"";"";"";"";"";"";"";"";"";"";"";"";"";"";"";"";"";"";"";"";"";"";"";"";"";"";
"10";"220R";"R-EU_R0805";"R0805";"R14, R15, R16, R17, R18, R19, R20, R21, R75, R81";"RESISTOR, European symbol";"";"";"";"";"";"";"";"";"";"";"";"";"";"";"";"";"";"";"";"";"";"";"";"";"";"";"86";"";"";"";"";"R";"";"";"";"";"";
"3";"220k";"R-EU_R0603";"R0603";"R2, R3, R42";"RESISTOR, European symbol";"";"";"";"";"";"";"";"";"";"";"";"";"";"";"";"";"";"";"";"";"";"";"";"";"";"";"70";"";"";"";"";"R";"";"";"";"";"";
"3";"220nF";"C-EUC0603";"C0603";"C34, C51, C57";"CAPACITOR, European symbol";"";"";"";"";"";"";"";"";"";"";"";"";"";"";"";"";"";"";"";"";"";"";"";"";"";"";"73";"";"";"";"";"C";"";"";"";"";"";
"4";"220u";"CPOL-EUE2.5-5";"E2,5-5";"C2, C3, C72, C80";"POLARIZED CAPACITOR, European symbol";"";"";"";"";"";"";"";"";"";"";"";"";"";"";"";"";"";"";"";"";"";"";"";"";"";"";"16";"";"";"";"";"C";"";"";"";"";"";
"1";"2N2222A";"BC547-NPN-TO92-CBE";"TO92-CBE";"T2";"NPN Transistror";"";"";"";"";"";"";"";"";"";"";"";"";"";"";"";"";"";"";"";"";"";"";"";"";"";"";"0";"";"";"";"";"";"";"";"";"";"";
"3";"39k";"R-EU_R0603";"R0603";"R35, R41, R46";"RESISTOR, European symbol";"";"";"";"";"";"";"";"";"";"";"";"";"";"";"";"";"";"";"";"";"";"";"";"";"";"";"70";"";"";"";"";"R";"";"";"";"";"";
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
